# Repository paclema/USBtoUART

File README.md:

# USBtoUART

A compact USB-C to UART bridge board based on the Silicon Labs CP2102N chip and featuring a dedicated XC6220B331ER LDO regulator, designed for debugging, programming, and serial communication with microcontrollers and embedded systems.

**Why this board?** Unlike typical USB-to-UART bridges, this board features a dedicated LDO regulator that supplies up to 1A at 3.3V, ensuring stable power delivery to the target board while providing reliable data communication.

<p align="center" width="100%">
  
</p>

| Top View | 3D Rendering | Bottom View |
|:--------:|:------------:|:-----------:|
|  |  |  |

## Features

- **USB-C Connector**: Modern USB-C interface for reliable power and data connection (USB 2.0)
- **CP2102N Bridge Chip**: High-performance USB to UART bridge controller (up to 3 Mbaud)
- **High-Power LDO**: Dedicated XC6220B331ER regulator providing up to 1A at 3.3V for connected devices (the CP2102N operates directly from USB 5V)
- **Status LEDs**: Visual indicators for Power (PWR), Transmit (TX), and Receive (RX)
- **UART Breakout**: Dedicated 6-pin UART connector with standard pinout
- **Extended GPIO Access & Breadboard Compatibility**: Exposes extra CP2102N GPIO pins via dual 10-pin headers, designed for direct insertion into standard breadboards to simplify prototyping and expand control options
- **Auto-Reset Circuit**: Dual MOSFET transistor circuit enables automatic reset of the connected microcontroller during programming
- **Compact Form Factor**: Optimized 2-layer PCB layout with surface-mount components (0805 package size)

## Pin Configuration

### UART Connector (J3)
> **Note:** In ESP8266 and ESP32 family chips, their GPIO0 pin is used to control boot mode (e.g., entering flash mode for programming). The labeled GPIO0 pin in this connector is intended to be connected to the target chip's GPIO0 pin to control the boot mode. This usage may not apply to other target chips, so verify your specific hardware requirements.
> 
| Pin | Function | Description |
|-----|----------|-------------|
| 1   | 3V3      | 3.3V Power Output |
| 2   | EN       | Enable/Reset |
| 3   | GPIO0    | Boot mode control |
| 4   | TXD      | UART Transmit |
| 5   | RXD      | UART Receive |
| 6   | GND      | Ground |

### Port Connectors (J2, J4)
- 10-pin male headers providing access to power rails (3.3V, 5V, GND) and CP2102N GPIO signals
- Enable powering and controlling external circuits directly from the board
- Compatible with standard breadboard and prototyping setups
- Standard 2.54mm (0.1") pin spacing

#### PORT1 Connector (J2)
| Pin | Function | Description |
|-----|----------|-------------|
| 1   | GPIO.6   | CP2102N GPIO 6 |
| 2   | GPIO.0   | CP2102N GPIO 0 |
| 3   | GPIO.1   | CP2102N GPIO 1 |
| 4   | GPIO.2   | CP2102N GPIO 2 |
| 5   | GPIO.3   | CP2102N GPIO 3 |
| 6   | CHR0     | Battery Charging Detection 0 |
| 7   | CHR1     | Battery Charging Detection 1 |
| 8   | CHREN    | Battery Charging Enable |
| 9   | SUSPEND  | USB Suspend State |
| 10  | /SUSPEND | USB Suspend State (Inverted) |

#### PORT2 Connector (J4)
| Pin | Function | Description |
|-----|----------|-------------|
| 1   | +5V      | 5V Power Output (from USB connector) |
| 2   | GPIO.5   | CP2102N GPIO 5 |
| 3   | GPIO.4   | CP2102N GPIO 4 |
| 4   | RTS      | Request To Send |
| 5   | CTS      | Clear To Send |
| 6   | DSR      | Data Set Ready |
| 7   | DTR      | Data Terminal Ready |
| 8   | DCD      | Data Carrier Detect |
| 9   | CLK      | Clock output |
| 10  | GND      | Ground |

## Getting Started

### Driver Installation

Download and install the CP210x Universal Windows Driver:
[CP210x Universal Windows Driver](https://www.silabs.com/developers/usb-to-uart-bridge-vcp-drivers?tab=downloads)

### Connection

1. Connect your target device to the UART connector (J3) or port headers
2. Connect the USB-C cable to your computer
3. The PWR LED should illuminate, indicating successful power connection
4. TX/RX LEDs will flash during data transmission

### Device Configuration

The CP2102N chip allows customization of USB device descriptors including vendor ID, product ID, serial number, and other parameters:

#### Using Silicon Labs Simplicity Studio 5:
1. Download and install **Simplicity Studio 5** from [Silicon Labs](https://www.silabs.com/developers/simplicity-studio)
2. Connect the USBtoUART board to your computer
3. Launch Simplicity Studio 5 and select your CP2102N device from the detected devices list
4. Navigate to **USBXpress™ Device Configuratior** utility
5. Configure device descriptors (Product String, Vendor and Product IDs, Serial Number, etc.) and save them to the device

## Project Files

This repository containes:

- **KiCad Project**: [`USBtoUART.kicad_pro`](USBtoUART.kicad_pro) - Main KiCad project file
- **Schematics**: [`USBtoUART.kicad_sch`](USBtoUART.kicad_sch) - Complete circuit design
- **PCB Layout**: [`USBtoUART.kicad_pcb`](USBtoUART.kicad_pcb) - 2-layer PCB design
- **Custom Libraries**: [`libs/`](libs/) - Project-specific symbols, footprints, and 3D models
- **Bill of Materials**: [`bom/v1.0/USBtoUART.csv`](bom/v1.0/USBtoUART.csv) - Complete component list
- **Interactive BOM**: [`bom/v1.0/ibom.html`](bom/v1.0/ibom.html) - Interactive Bill of Materials
- **Gerber Files**: [`gerber/v1.0/`](gerber/v1.0/) - Manufacturing files
- **Documentation**: 
  - **Schematic PDF**: [`doc/v1.0/USBtoUART_sch.pdf`](doc/v1.0/USBtoUART_sch.pdf)
  - **PCB Layout PDFs**: [`doc/v1.0/USBtoUART_brd_top.pdf`](doc/v1.0/USBtoUART_brd_top.pdf), [`doc/v1.0/USBtoUART_brd_bottom.pdf`](doc/v1.0/USBtoUART_brd_bottom.pdf), [`doc/v1.0/USBtoUART_brd_layers.pdf`](doc/v1.0/USBtoUART_brd_layers.pdf)
  - **3D Model**: [`doc/v1.0/USBtoUART.step`](doc/v1.0/USBtoUART.step) - 3D model of the assembled USBtoUART board
  - **Board Images**: [`doc/v1.0/`](doc/v1.0/)

## Manufacturing

The board is designed for standard PCB manufacturing processes:
- **PCB Thickness**: 1.6mm
- **Minimum Track/Space**: 0.1mm/0.1mm
- **Minimum Via**: 0.2mm
- **Surface Finish**: HASL or ENIG recommended

## Version History

- **v1.0**: First release

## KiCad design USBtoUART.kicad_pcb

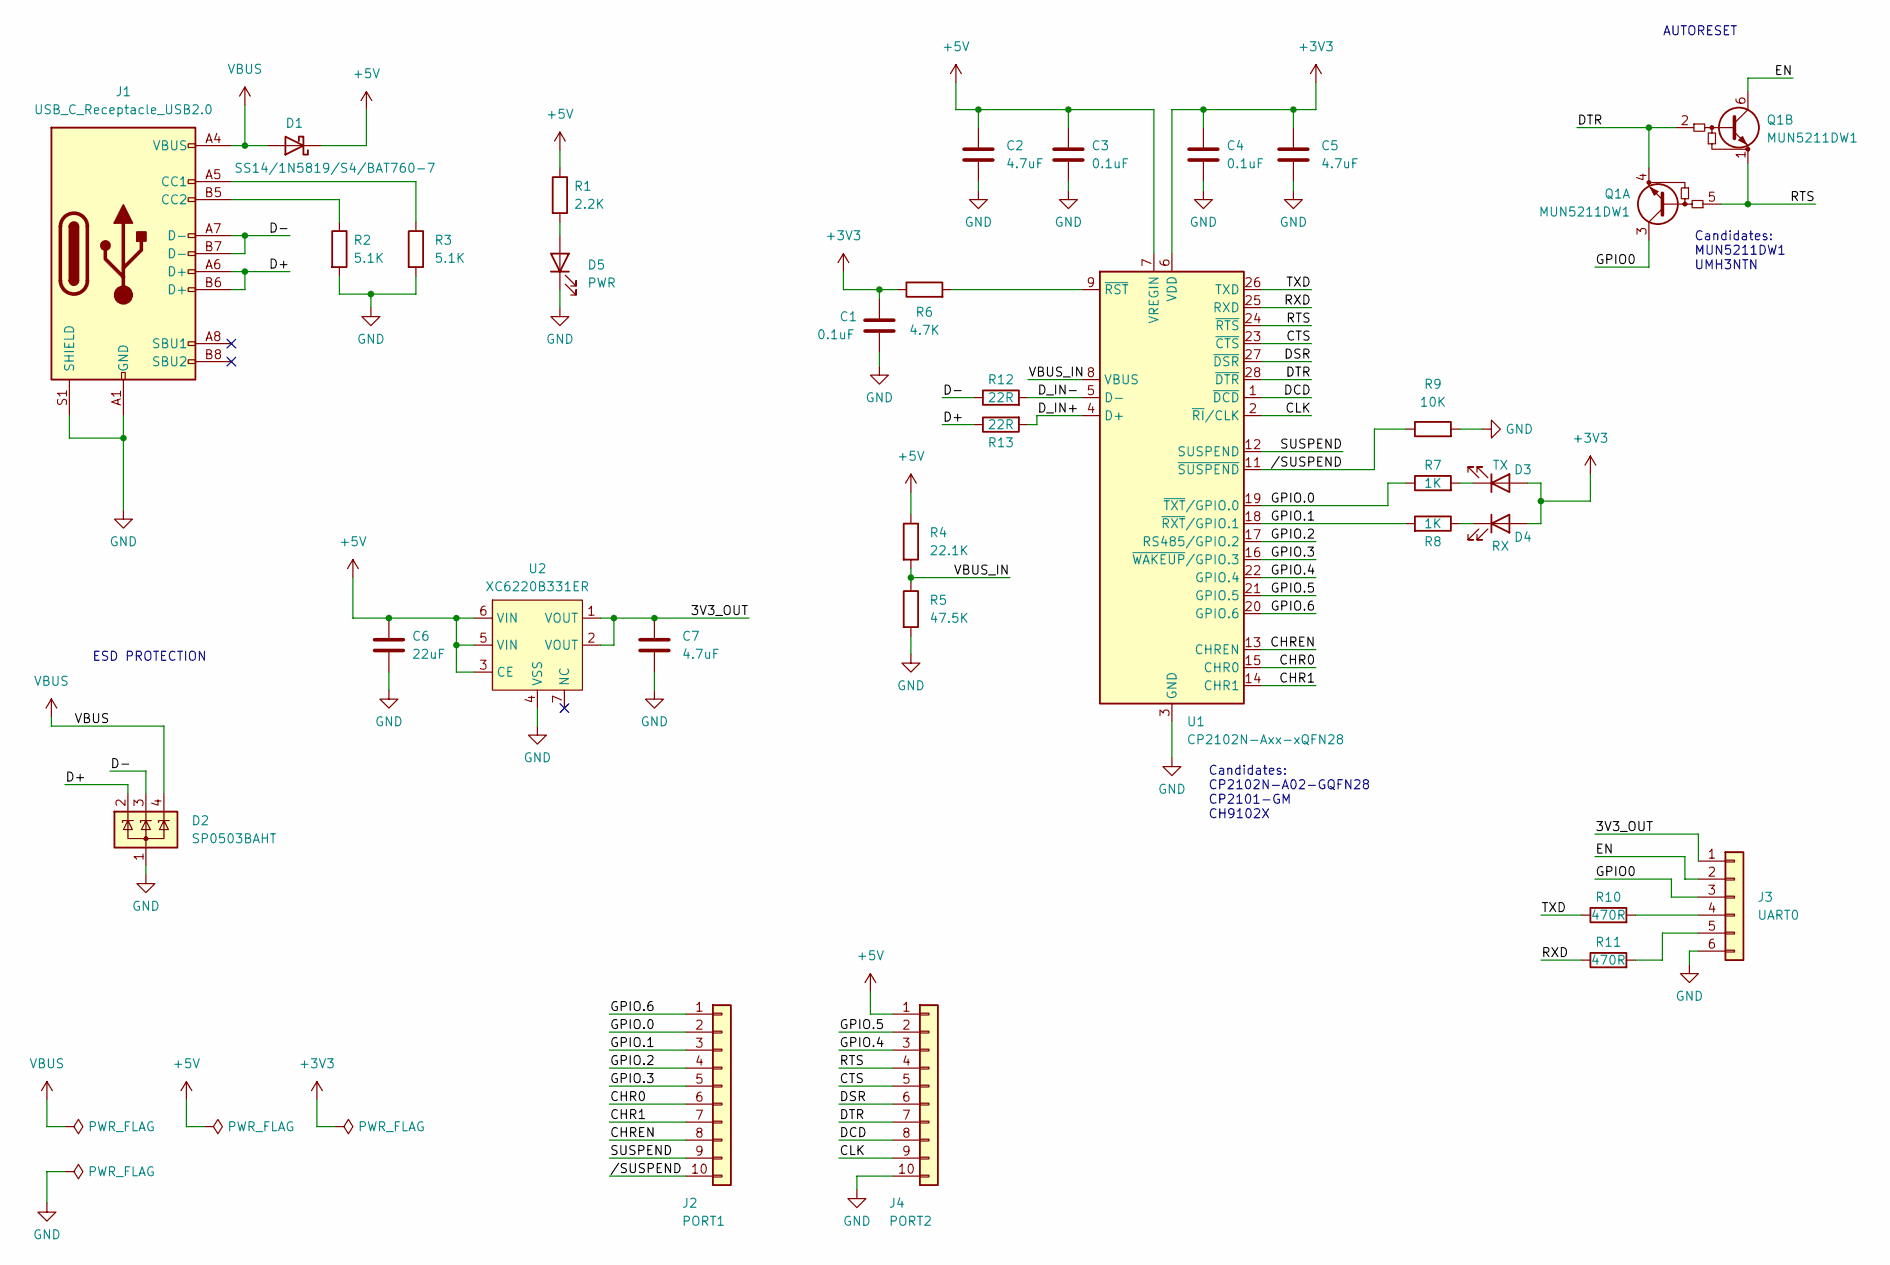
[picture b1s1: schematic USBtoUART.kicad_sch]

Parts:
C1, C3, C4: 0.1uF; C_0805_2012Metric; Mouser PN C0805C104K5RAC7411
C2, C5, C7: 4.7uF; C_0805_2012Metric; Mouser PN GRM21BR71C475KE51L
C6: 22uF; C_0805_2012Metric; Mouser PN GRM21BD71A226ME44L
D1: SS14/1N5819/S4/BAT760-7; SOD-123EP; Mouser PN SS14FP
D2: SP0503BAHT; SOT-143; Mouser PN SP0503BAHTG
D3: TX; LED_0805_2012Metric; Mouser PN LTST-C170GKT
D4: RX; LED_0805_2012Metric; Mouser PN LTST-C170KFKT
D5: PWR; LED_0805_2012Metric; Mouser PN 150080BS75000
J1: USB_C_Receptacle_USB2.0; USB_C_Receptacle_Molex_216990-001; Mouser PN 216990-0001
J2: PORT1; PinHeader_1x10_P2.54mm_Vertical
J3: UART0; PinHeader_1x06_P2.54mm_Vertical
J4: PORT2; PinHeader_1x10_P2.54mm_Vertical
Q1: MUN5211DW1; SOT-363_SC-70-6; Mouser PN MUN5211DW1T1G
R1: 2.2K; R_0805_2012Metric; Mouser PN AC0805FR-072K2L
R2, R3: 5.1K; R_0805_2012Metric; Mouser PN AC0805FR-075K1L
R4: 22.1K; R_0805_2012Metric; Mouser PN AC0805FR-0722K1L
R5: 47.5K; R_0805_2012Metric; Mouser PN AC0805FR-7W47K5L
R6: 4.7K; R_0805_2012Metric; Mouser PN AC0805FR-074K7L
R7, R8: 1K; R_0805_2012Metric; Mouser PN AC0805FR-071KL
R9: 10K; R_0805_2012Metric; Mouser PN AC0805FR-7W10KL
R10, R11: 470R; R_0805_2012Metric; Mouser PN AC0805FR-07470RL
R12, R13: 22R; R_0805_2012Metric; Mouser PN AC0805FR-0722RL
U1: CP2102N-Axx-xQFN28; QFN-28-1EP_5x5mm_P0.5mm_EP3.35x3.35mm_ThermalVias; Mouser PN CP2102N-A02-GQFN28
U2: XC6220B331ER; USP-6C; Mouser PN XC6220B331ER-G

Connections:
+3V3: C1.1, C4.1, C5.1, D3.2 (A), D4.2 (A), R6.1, U1.6 (VDD)
+5V: C2.1, C3.1, C6.1, D1.1 (K), J4.1, R1.1, R4.1, U1.7 (VREGIN), U2.3 (CE), U2.5 (VIN), U2.6 (VIN)
/3V3_OUT: C7.1, J3.1, U2.1 (VOUT), U2.2 (VOUT)
/CHR0: J2.6, U1.15 (CHR0)
/CHR1: J2.7, U1.14 (CHR1)
/CHREN: J2.8, U1.13 (CHREN)
/CLK: J4.9, U1.2 (~RI/CLK)
/CTS: J4.5, U1.23 (~CTS)
/D+: D2.2 (K), J1.A6 (D+), J1.B6 (D+), R13.1
/D-: D2.3 (K), J1.A7 (D-), J1.B7 (D-), R12.1
/DCD: J4.8, U1.1 (~DCD)
/DSR: J4.6, U1.27 (~DSR)
/DTR: J4.7, Q1.2 (B2), Q1.4 (E1), U1.28 (~DTR)
/D_IN+: R13.2, U1.4 (D+)
/D_IN-: R12.2, U1.5 (D-)
/EN: J3.2, Q1.6 (C2)
/GPIO0: J3.3, Q1.3 (C1)
/GPIO.0: J2.2, R7.1, U1.19 (~TXT/GPIO.0)
/GPIO.1: J2.3, R8.2, U1.18 (~RXT/GPIO.1)
/GPIO.2: J2.4, U1.17 (RS485/GPIO.2)
/GPIO.3: J2.5, U1.16 (~WAKEUP/GPIO.3)
/GPIO.4: J4.3, U1.22 (GPIO.4)
/GPIO.5: J4.2, U1.21 (GPIO.5)
/GPIO.6: J2.1, U1.20 (GPIO.6)
/RTS: J4.4, Q1.1 (E2), Q1.5 (B1), U1.24 (~RTS)
/RXD: R11.1, U1.25 (RXD)
/SUSPEND: J2.9, U1.12 (SUSPEND)
/TXD: R10.1, U1.26 (TXD)
/VBUS_IN: R4.2, R5.1, U1.8 (VBUS)
//SUSPEND: J2.10, R9.1, U1.11 (~SUSPEND)
GND: C1.2, C2.2, C3.2, C4.2, C5.2, C6.2, C7.2, D2.1 (A), D5.1 (K), J1.A1 (GND), J1.A12 (GND), J1.B1 (GND), J1.B12 (GND), J1.S1 (SHIELD), J3.6, J4.10, R2.2, R3.2, R5.2, R9.2, U1.3 (GND), U1.29 (GND), U2.4 (VSS)
unnamed: D3.1 (K), R7.2
unnamed: D4.1 (K), R8.1
unnamed: D5.2 (A), R1.2
unnamed: J1.A5 (CC1), R3.1
unnamed: J1.B5 (CC2), R2.1
unnamed: J3.4, R10.2
unnamed: J3.5, R11.2
unnamed: R6.2, U1.9 (~RST)
VBUS: D1.2 (A), D2.4 (K), J1.A4 (VBUS), J1.A9 (VBUS), J1.B4 (VBUS), J1.B9 (VBUS)

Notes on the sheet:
Candidates: MUN5211DW1 UMH3NTN
Candidates: CP2102N-A02-GQFN28 CP2101-GM CH9102X
AUTORESET
ESD PROTECTION

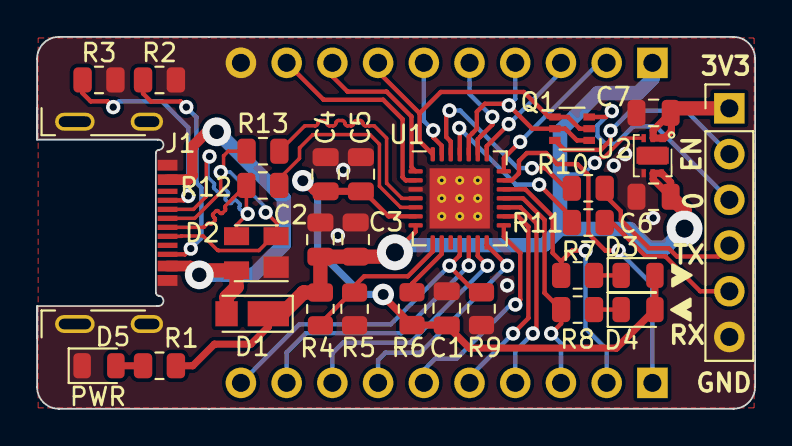
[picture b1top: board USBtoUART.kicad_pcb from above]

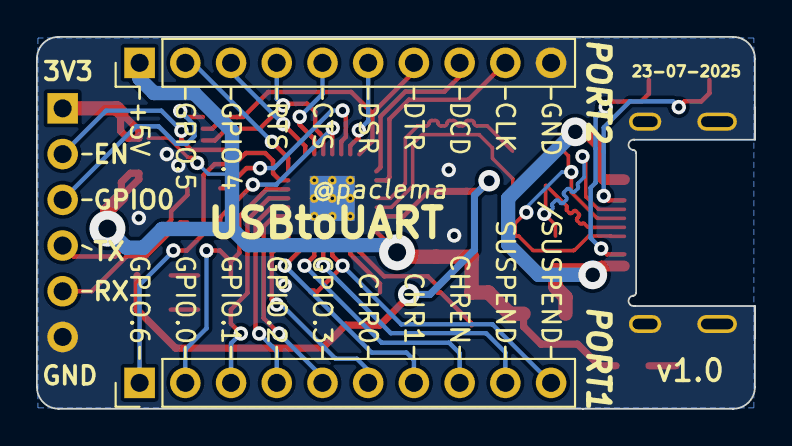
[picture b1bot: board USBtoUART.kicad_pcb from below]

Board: 2 copper layers, 39.9 x 20.6 mm, 32 parts (2 on the bottom side), 40 nets.

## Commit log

2025-07-23 Add USBtoUART sch, pcb, symbols, footprints, 3d models and bom for version v1.0
2025-07-23 Update README.md for CP210x Universal Windows Driver
2025-07-24 Add doc files including exported pdf for sch & brd and images for USBtoUART v1.0
2025-07-24 Export gerber files for USBtoUART v1.0
2025-07-24 Update README.md to enhance board description, features, and usage instructions for USBtoUART
2025-07-24 Update README.md to clarify project files
2025-07-29 Add real image of USBtoUART board to README.md
2025-07-29 Add USBtoUART gItf 3D files
2025-07-29 Remove version on pdf file names
2025-07-29 Update 3D files with routing and silkscreen
2025-07-29 Fix USBtoUART.gltf with correct name for bin
